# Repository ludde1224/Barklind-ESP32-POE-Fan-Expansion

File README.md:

# Barklind-ESP32-POE-Fan-Expansion
Circuit that allows for controlling and powering 4 pin pwm fans using an Olimex ESP32-POE

For overview of latest schematic, check out [Barklind PDF Schematic](docs/Schematic/Barklind-schematic.pdf)

# PCB Render

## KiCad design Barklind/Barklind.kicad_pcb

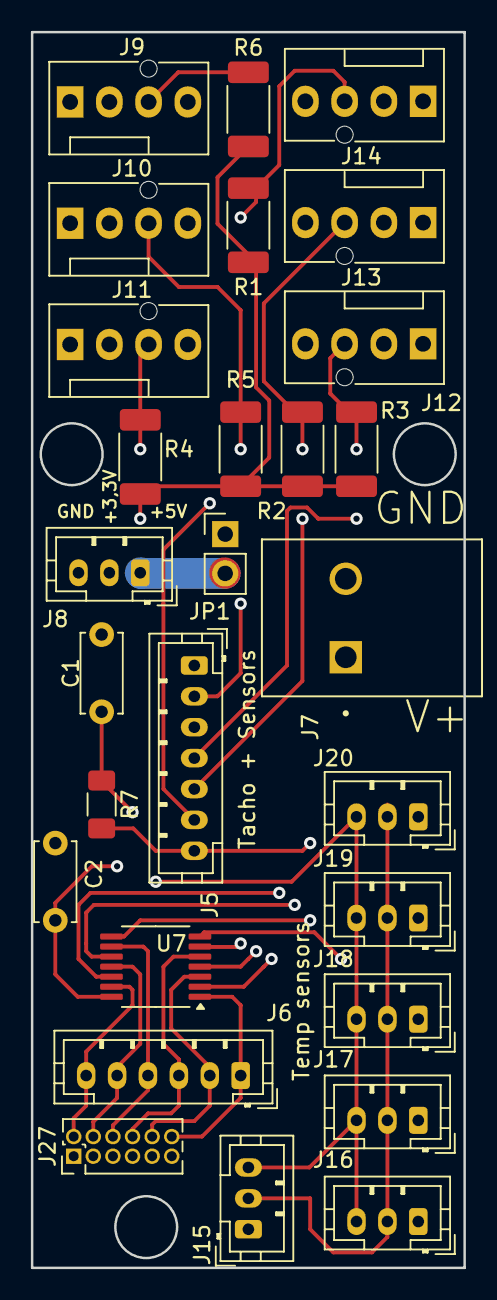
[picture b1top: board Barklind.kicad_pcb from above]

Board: 4 copper layers, 28.0 x 80.0 mm, 28 parts (0 on the bottom side), 23 nets.

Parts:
C1, C2: 100 nF; C_Disc_D5.0mm_W2.5mm_P5.00mm
J5: Conn_01x07_Pin; JST_PH_B7B-PH-K_1x07_P2.00mm_Vertical
J6: Conn_01x06_Pin; JST_PH_B6B-PH-K_1x06_P2.00mm_Vertical
J7: Conn_01x02_Pin; PHOENIX_1705469
J8, J15, J16, J17, J18, J19, J20: Conn_01x03_Pin; JST_PH_B3B-PH-K_1x03_P2.00mm_Vertical
J9, J10, J11, J12, J13, J14: Conn_01x04_Pin; FanPinHeader_1x04_P2.54mm_Vertical
J27: Conn_02x06_Odd_Even; PinHeader_2x06_P1.27mm_Vertical
JP1: Jumper_2_Open; PinHeader_1x02_P2.54mm_Vertical
R1, R2, R3, R4, R5, R6: 10k; R_2010_5025Metric_Pad1.40x2.65mm_HandSolder
R7: 4,7k; R_1206_3216Metric_Pad1.30x1.75mm_HandSolder
U7: 74HCT04; TSSOP-14_4.4x5mm_P0.65mm

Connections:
/Signal conditioning/FanSupply: J7.1, J9.2, J10.2, J11.2, J12.2, J13.2, J14.2, JP1.1
/Signal conditioning/GND: C1.1, C2.1, J7.2, J8.3, J9.1, J10.1, J11.1, J12.1, J13.1, J14.1, J15.1, J16.1, J17.1, J18.1, J19.1, J20.1, J27.1, J27.3, J27.5, J27.7, J27.9, J27.11, U7.7 (GND)
/Signal conditioning/Supply5V: C2.2, J8.1, JP1.2, U7.14 (VCC)
unnamed: J5.1, J9.3, R6.2
unnamed: J9.4, U7.2
unnamed: J5.2, J10.3, R5.2
unnamed: J10.4, U7.4
unnamed: J5.3, J11.3, R4.2
unnamed: J11.4, U7.6
unnamed: J5.4, J12.3, R3.2
unnamed: J12.4, U7.8
unnamed: J5.5, J13.3, R2.2
unnamed: J13.4, U7.10
unnamed: J5.6, J14.3, R1.2
unnamed: J14.4, U7.12
unnamed: J5.7, J15.2, J16.2, J17.2, J18.2, J19.2, J20.2, R7.2
unnamed: C1.2, J8.2, J15.3, J16.3, J17.3, J18.3, J19.3, J20.3, R1.1, R2.1, R3.1, R4.1, R5.1, R6.1, R7.1
unnamed: J6.6, J27.2, U7.13
unnamed: J6.5, J27.4, U7.11
unnamed: J6.4, J27.6, U7.9
unnamed: J6.3, J27.8, U7.5
unnamed: J6.2, J27.10, U7.3
unnamed: J6.1, J27.12, U7.1

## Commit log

2024-11-19 Added espressif Kicad library as submodule
2024-11-19 Setup espressif library as project library with relative path
2024-11-19 Move and rename submodule kicad-libraries
2024-11-19 Changed library links Added project library Added component suggestions Made basic schematic for pwm CMOS driver
2024-11-24 Added PoE Hierarchical sheet Added RJ45 connector with PoE support Changed from fans in schematic to generic 4 pin connectors
2024-11-24 Added plot for current schematic
2024-11-24 Added suggestions file with first suggestion
2024-11-24 Added link to latest schematic in README
2024-11-24 Fixed spelling error in new link...
2024-11-26 Added Ethercat schematic Added W5500 to component suggestions Added picture to explain CD4007UB wiring
2024-11-26 Updated gitignore to not include vscode dir Added KiBot workflows
2024-11-26 Test of KiBot workflow Removed KiBot suggestion
2024-11-26 Fixed error in schematic file ending in KiBot workflow
2024-11-26 Added comment in schematic to test workflow
2024-11-26 Disabled erc/drc checks for the current workflow
2024-11-26 Added comment on schematic to test workflow export
2024-11-26 Updated kibot job actions references
2024-11-26 Comment for testing
2024-11-26 Commented out ibom generation
2024-11-26 Added another comment to schematic for workflow testing
2024-11-28 Added ESP32-DevkitC Updated workflow to commit changes (adding built docs) Removed manually exported PDF schematic in favour of auto-exported schematic
2024-11-28 Update authentication in workflow
2024-11-28 Added manual trigger possibility to workflow
2024-11-28 Added branch reference to action git push
2024-11-28 Changed workflow to only trigger on pushes
2024-11-28 Pulled KiBot.yml from dev branch
2024-11-28 Update docs with KiBot results
2024-11-28 Updated readme with KiBot action badge and updated schematic link
2024-11-28 Added CONTRIBUTING.md
2024-11-28 Fix readme link
2024-11-28 Added most components to Ethernet schematic Updated main schematic to add connections to/from ethernet schematic Added connections from ESP32 to Fan driver
2024-11-28 Added diff schematic to only output files that are different
2024-11-28 changed config.kibot.yaml to troubleshoot schematic diff
2024-11-28 fixed spelling error in config
2024-11-28 Added fetch depth option for checkout to allow diff to search properly
2024-11-29 Added and connected ESP32-Pin-Headers
2024-11-29 Added basic board (with no layout specified) Added additional comments to schematic
2024-11-29 Added pcb render output
2024-11-29 Imported pcb render to README
2024-11-29 Trying out different angle for PCB render
2024-11-29 Commented out diff since it is not functional currently
2024-11-29 Changed angle again
2024-11-30 More changes to output rotation
2024-11-30 Yet another angle change
2024-11-30 Added KiCad and KiBot version badges to readme
2025-01-05 Hello world
2025-01-06 Assigned footprints to multiple symbols Removed automatic workflow triggering. Will change in the future
2025-01-06 Pushed without lock files
2025-02-01 Added PCB
2025-02-02 Restructured project, Changed kibot configurations into different files Changed github actions for the different jobs
2025-02-02 Updated Kicad-libraries
2025-02-02 Added changes to kibot actions
2025-02-02 Removed archived items from docs Changed back kibot to run all jobs on any change to schematic or pcb (temporary fix)
2025-02-02 Added text to schematic to troubleshoot workflow
2025-02-02 Removed ERC-check and added continue on error to jobs
2025-02-02 Test for github pages
2025-02-02 Fixed the index file
2025-02-21 Added pin header for pulling down unused inverter inputs
2025-03-13 Changed PCB to 4 layer and created manufacture files
2025-03-13 Separated signal GND and Power GND
